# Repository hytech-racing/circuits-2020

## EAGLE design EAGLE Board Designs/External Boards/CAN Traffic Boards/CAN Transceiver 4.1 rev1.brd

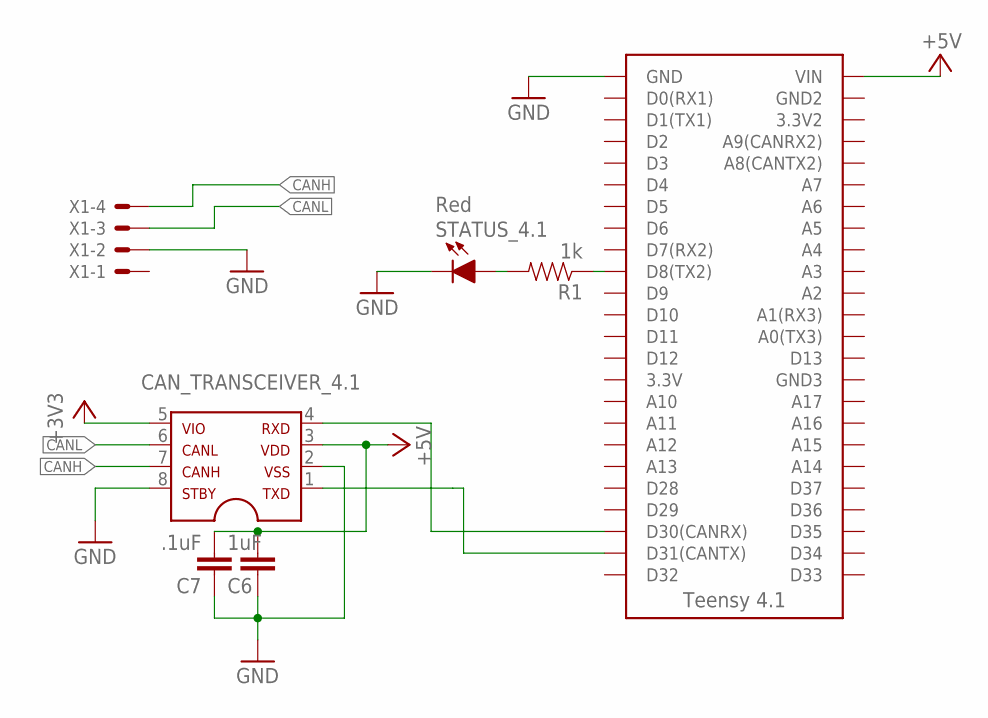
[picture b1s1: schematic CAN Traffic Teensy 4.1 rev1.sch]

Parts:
C6: 1uF; 0603-CAP
C7: .1uF; 0603-CAP
CAN_TRANSCEIVER_4.1: MCP2562SOIC-08; SOIC-08
R1: 1k; 0603-RES
STATUS_4.1: Red; LED-805
U$2: TEENSY_4.1_SIMPLE
X1: CONNECTOR-4NANO-FIT_RIGHT_ANGLE-4-SURFACE; NANO-FIT_RIGHT_ANGLE-4-SURFACE

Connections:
+3V3: CAN_TRANSCEIVER_4.1.5
+5V: C6.1, C7.1, CAN_TRANSCEIVER_4.1.3, U$2.VIN
CANH: CAN_TRANSCEIVER_4.1.7, X1.4
CANL: CAN_TRANSCEIVER_4.1.6, X1.3
GND: C6.2, C7.2, CAN_TRANSCEIVER_4.1.2, STATUS_4.1.C, U$2.GND, X1.2
unnamed: CAN_TRANSCEIVER_4.1.4, U$2.D30(CANRX)
unnamed: CAN_TRANSCEIVER_4.1.1, U$2.D31(CANTX)
unnamed: R1.2, STATUS_4.1.A
unnamed: R1.1, U$2.D8(TX2)

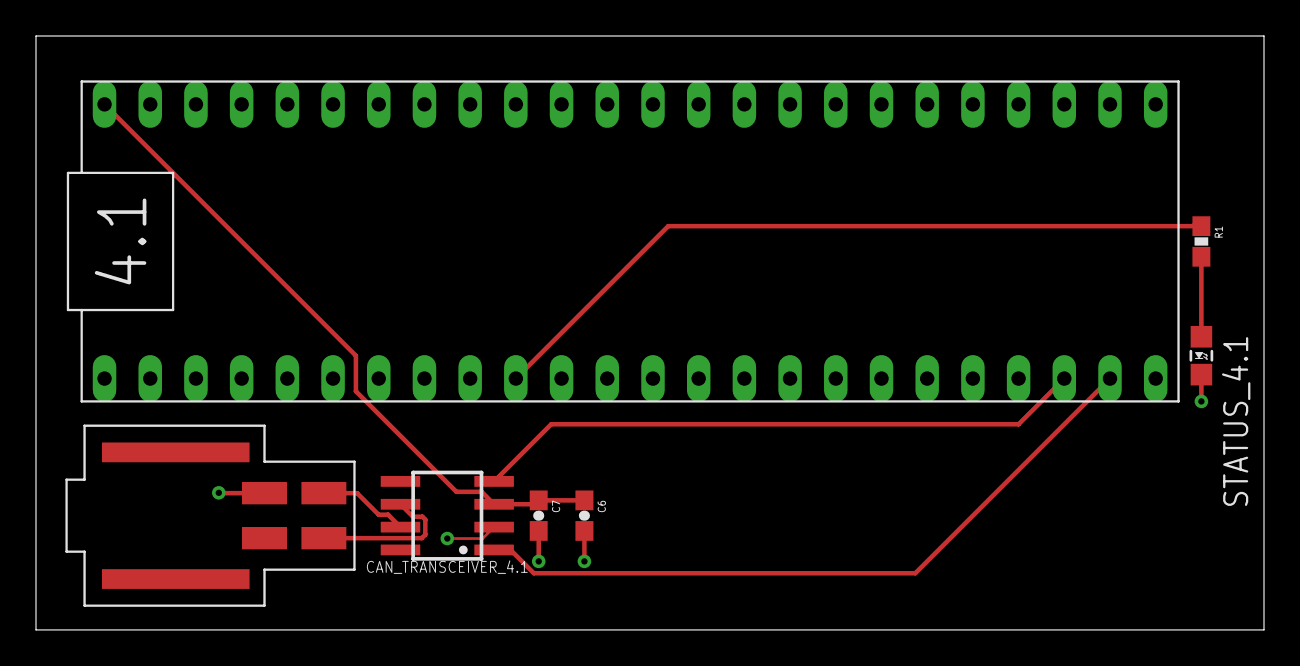
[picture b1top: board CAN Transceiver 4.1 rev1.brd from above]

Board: 2 copper layers, 68.2 x 33.0 mm, 7 parts (0 on the bottom side), 8 nets.

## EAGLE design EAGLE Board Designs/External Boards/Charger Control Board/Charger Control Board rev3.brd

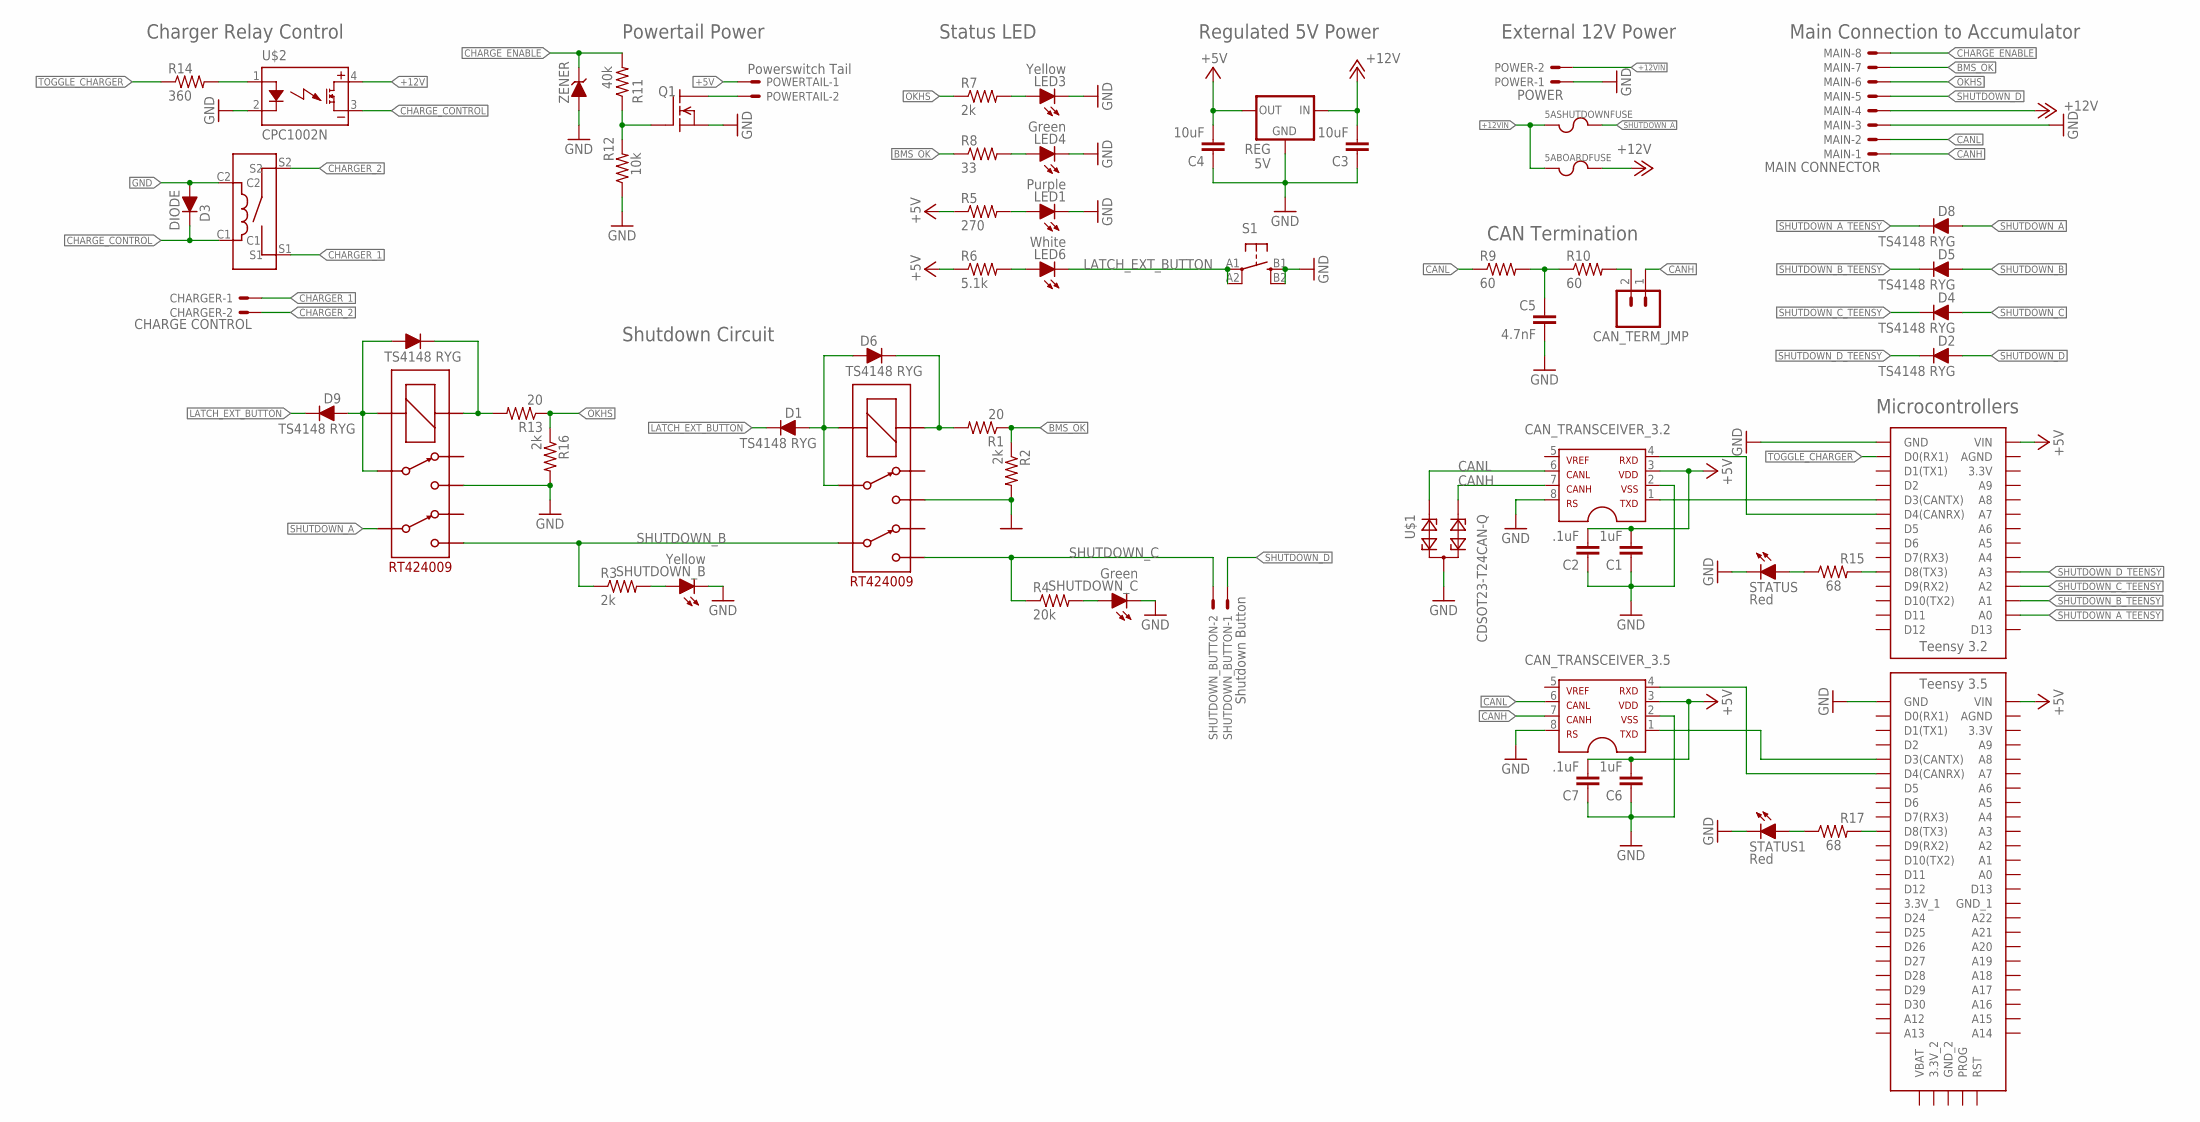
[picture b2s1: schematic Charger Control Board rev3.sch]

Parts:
5ABOARDFUSE, 5ASHUTDOWNFUSE: FUSE_MINIBLADE; MINI-BLADE_FUSE_HOLDER; RATING 5A
BMS_SHUTDOWN_RLY: RT424009; RELAY_DPDT
C1, C6: 1uF; 0805; TOLERANCE 5%; VOLTAGE 10V
C2, C7: .1uF; 0805; TOLERANCE 5%; VOLTAGE 10V
C3: 10uF; 0805; TOLERANCE 1%; VOLTAGE 25V
C4: 10uF; 0805; TOLERANCE 5%; VOLTAGE 25V
C5: 4.7nF; 0805; TOLERANCE 5%; VOLTAGE 50V
CAN_TERM_JMP: M02_SLIM; 1X02_SLIM
CAN_TRANSCEIVER_3.2, CAN_TRANSCEIVER_3.5: MCP2551; SOIC-08
CHARGER: CHARGE CONTROL; NANO-FIT_VERTICAL-2
D1, D2, D4, D5, D6, D7, D8, D9: TS4148 RYG; 0805_D
D3: DIODE; 0805_D
IMD_SHUTDOWN_RLY: RT424009; RELAY_DPDT
LED1: Purple; LED-805
LED3: Yellow; LED-805
LED4: Green; LED-805
LED6: White; LED-805
MAIN: MAIN CONNECTOR; NANO-FIT_VERTICAL-8
POWER: POWER; NANO-FIT_VERTICAL-2
POWERTAIL: Powerswitch Tail; NANO-FIT_VERTICAL-2
Q1: DMG3406LSOT; SOT23
R1, R13: 20; 0805; TOLERANCE 1%
R2, R3, R7, R16: 2k; 0805; TOLERANCE 1%
R4: 20k; 0805; TOLERANCE 1%
R5: 270; 0805; TOLERANCE 1%
R6: 5.1k; 0805; TOLERANCE 1%
R8: 33; 0805; TOLERANCE 1%
R9, R10: 60; 0805; TOLERANCE 1%
R11: 40k; 0805; TOLERANCE 1%
R12: 10k; 0805; TOLERANCE 1%
R14: 360; 0805; TOLERANCE 1%
R15, R17: 68; 0805; TOLERANCE 1%
REG: 5V; OKI-78SR
S1: BTN_10-XXSMD; TACTILE_SWITCH_SMD_6.2MM_TALL
SHUTDOWN_B: Yellow; LED-805
SHUTDOWN_BUTTON: Shutdown Button; NANO-FIT_VERTICAL-2
SHUTDOWN_C: Green; LED-805
STATUS, STATUS1: Red; LED-805
U$1: CDSOT23-T24CAN-Q; SOT23
U$2: CPC1002N; SOP04
U$3: KT12-1A-40L-THT
U$4: TEENSY_3.2_SIMPLE
U$5: TEENSY_3.5_EXT
ZENER: DIODE_ZENER; SOT23

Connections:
+5V: C1.2, C2.2, C4.2, C6.2, C7.2, CAN_TRANSCEIVER_3.2.3, CAN_TRANSCEIVER_3.5.3, POWERTAIL.P$1, R5.1, R6.1, REG.3 (OUT), U$4.VIN, U$5.VIN
+12V: 5ABOARDFUSE.R1 (2), 5ABOARDFUSE.R2 (2), C3.2, MAIN.P$4, REG.1 (IN), U$2.4 (DC+)
+12VIN: 5ABOARDFUSE.L1 (1), 5ABOARDFUSE.L2 (1), 5ASHUTDOWNFUSE.L1 (1), 5ASHUTDOWNFUSE.L2 (1), POWER.P$2
BMS_OK: MAIN.P$7, R1.1, R2.1, R8.1
BMS_OK_RELAY: BMS_SHUTDOWN_RLY.COIL+, D6.C, R1.2
BMS_PWR_STEP: BMS_SHUTDOWN_RLY.3, BMS_SHUTDOWN_RLY.COIL-, D1.A, D6.A
CANH: CAN_TERM_JMP.1, CAN_TRANSCEIVER_3.2.7, CAN_TRANSCEIVER_3.5.7, MAIN.P$1, U$1.2
CANL: CAN_TRANSCEIVER_3.2.6, CAN_TRANSCEIVER_3.5.6, MAIN.P$2, R9.1, U$1.1
CHARGER_1: CHARGER.P$1, U$3.S1
CHARGER_2: CHARGER.P$2, U$3.S2
CHARGE_CONTROL: D3.C, U$2.3 (DC-), U$3.C1
CHARGE_ENABLE: MAIN.P$8, R11.2, ZENER.3 (C)
GND: C1.1, C2.1, C3.1, C4.1, C5.2, C6.1, C7.1, CAN_TRANSCEIVER_3.2.2, CAN_TRANSCEIVER_3.2.8, CAN_TRANSCEIVER_3.5.2, CAN_TRANSCEIVER_3.5.8, D3.A, LED1.C, LED3.C, LED4.C, MAIN.P$3, POWER.P$1, Q1.2 (S), R12.1, REG.2 (GND), S1.B1 (S), S1.B2 (S1), SHUTDOWN_B.C, SHUTDOWN_C.C, STATUS.C, STATUS1.C, U$1.3, U$2.2 (CONTROL-), U$3.C2, U$4.GND, U$5.GND, ZENER.1 (A)
IMD_PWR_STEP: D7.A, D9.A, IMD_SHUTDOWN_RLY.3, IMD_SHUTDOWN_RLY.COIL-
LATCH_EXT_BUTTON: D1.C, D9.C, LED6.C, S1.A1, S1.A2 (P1)
unnamed: POWERTAIL.P$2, Q1.3 (D)
unnamed: LED6.A, R6.2
unnamed: LED4.A, R8.2
unnamed: CAN_TRANSCEIVER_3.5.4, U$5.D4(CANRX)
unnamed: Q1.1 (G), R11.1, R12.2
unnamed: CAN_TRANSCEIVER_3.5.1, U$5.D3(CANTX)
unnamed: R17.1, STATUS1.A
unnamed: R15.1, STATUS.A
unnamed: R17.2, U$5.D8(TX3)
unnamed: R14.2, U$2.1 (CONTROL+)
unnamed: R15.2, U$4.D8(TX3)
unnamed: D7.C, IMD_SHUTDOWN_RLY.COIL+, R13.2
unnamed: CAN_TRANSCEIVER_3.2.4, U$4.D4(CANRX)
unnamed: CAN_TERM_JMP.2, R10.2
unnamed: R3.2, SHUTDOWN_B.A
unnamed: CAN_TRANSCEIVER_3.2.1, U$4.D3(CANTX)
unnamed: LED3.A, R7.2
unnamed: LED1.A, R5.2
unnamed: R4.2, SHUTDOWN_C.A
unnamed: BMS_SHUTDOWN_RLY.4, IMD_SHUTDOWN_RLY.4, R2.2, R16.2
unnamed: C5.1, R9.2, R10.1
OKHS: MAIN.P$6, R7.1, R13.1, R16.1
SHUTDOWN_A: 5ASHUTDOWNFUSE.R1 (2), 5ASHUTDOWNFUSE.R2 (2), D8.A, IMD_SHUTDOWN_RLY.6
SHUTDOWN_A_TEENSY: D8.C, U$4.A0
SHUTDOWN_B: BMS_SHUTDOWN_RLY.6, D5.A, IMD_SHUTDOWN_RLY.5, R3.1
SHUTDOWN_B_TEENSY: D5.C, U$4.A1
SHUTDOWN_C: BMS_SHUTDOWN_RLY.5, D4.A, R4.1, SHUTDOWN_BUTTON.P$2
SHUTDOWN_C_TEENSY: D4.C, U$4.A2
SHUTDOWN_D: D2.A, MAIN.P$5, SHUTDOWN_BUTTON.P$1
SHUTDOWN_D_TEENSY: D2.C, U$4.A3
TOGGLE_CHARGER: R14.1, U$4.D0(RX1)

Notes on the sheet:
Main Connection to Accumulator
External 12V Power
Powertail Power
Charger Relay Control
Regulated 5V Power
CAN Termination
Microcontrollers
Shutdown Circuit
Status LED

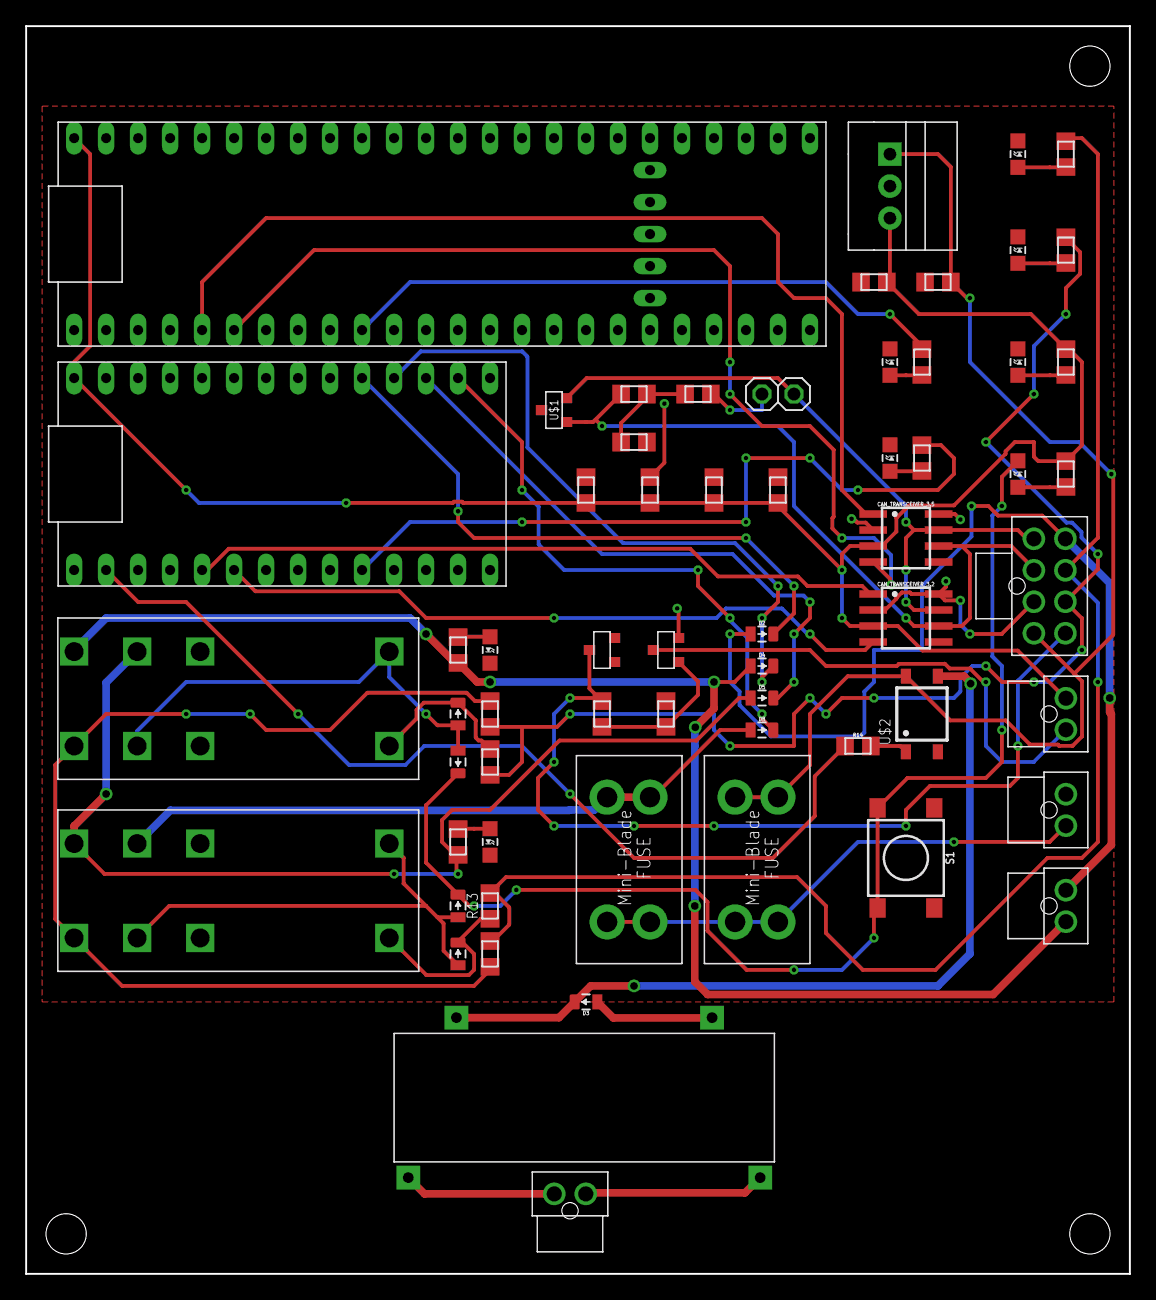
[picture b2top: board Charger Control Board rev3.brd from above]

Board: 2 copper layers, 87.6 x 99.1 mm, 62 parts (0 on the bottom side), 46 nets.

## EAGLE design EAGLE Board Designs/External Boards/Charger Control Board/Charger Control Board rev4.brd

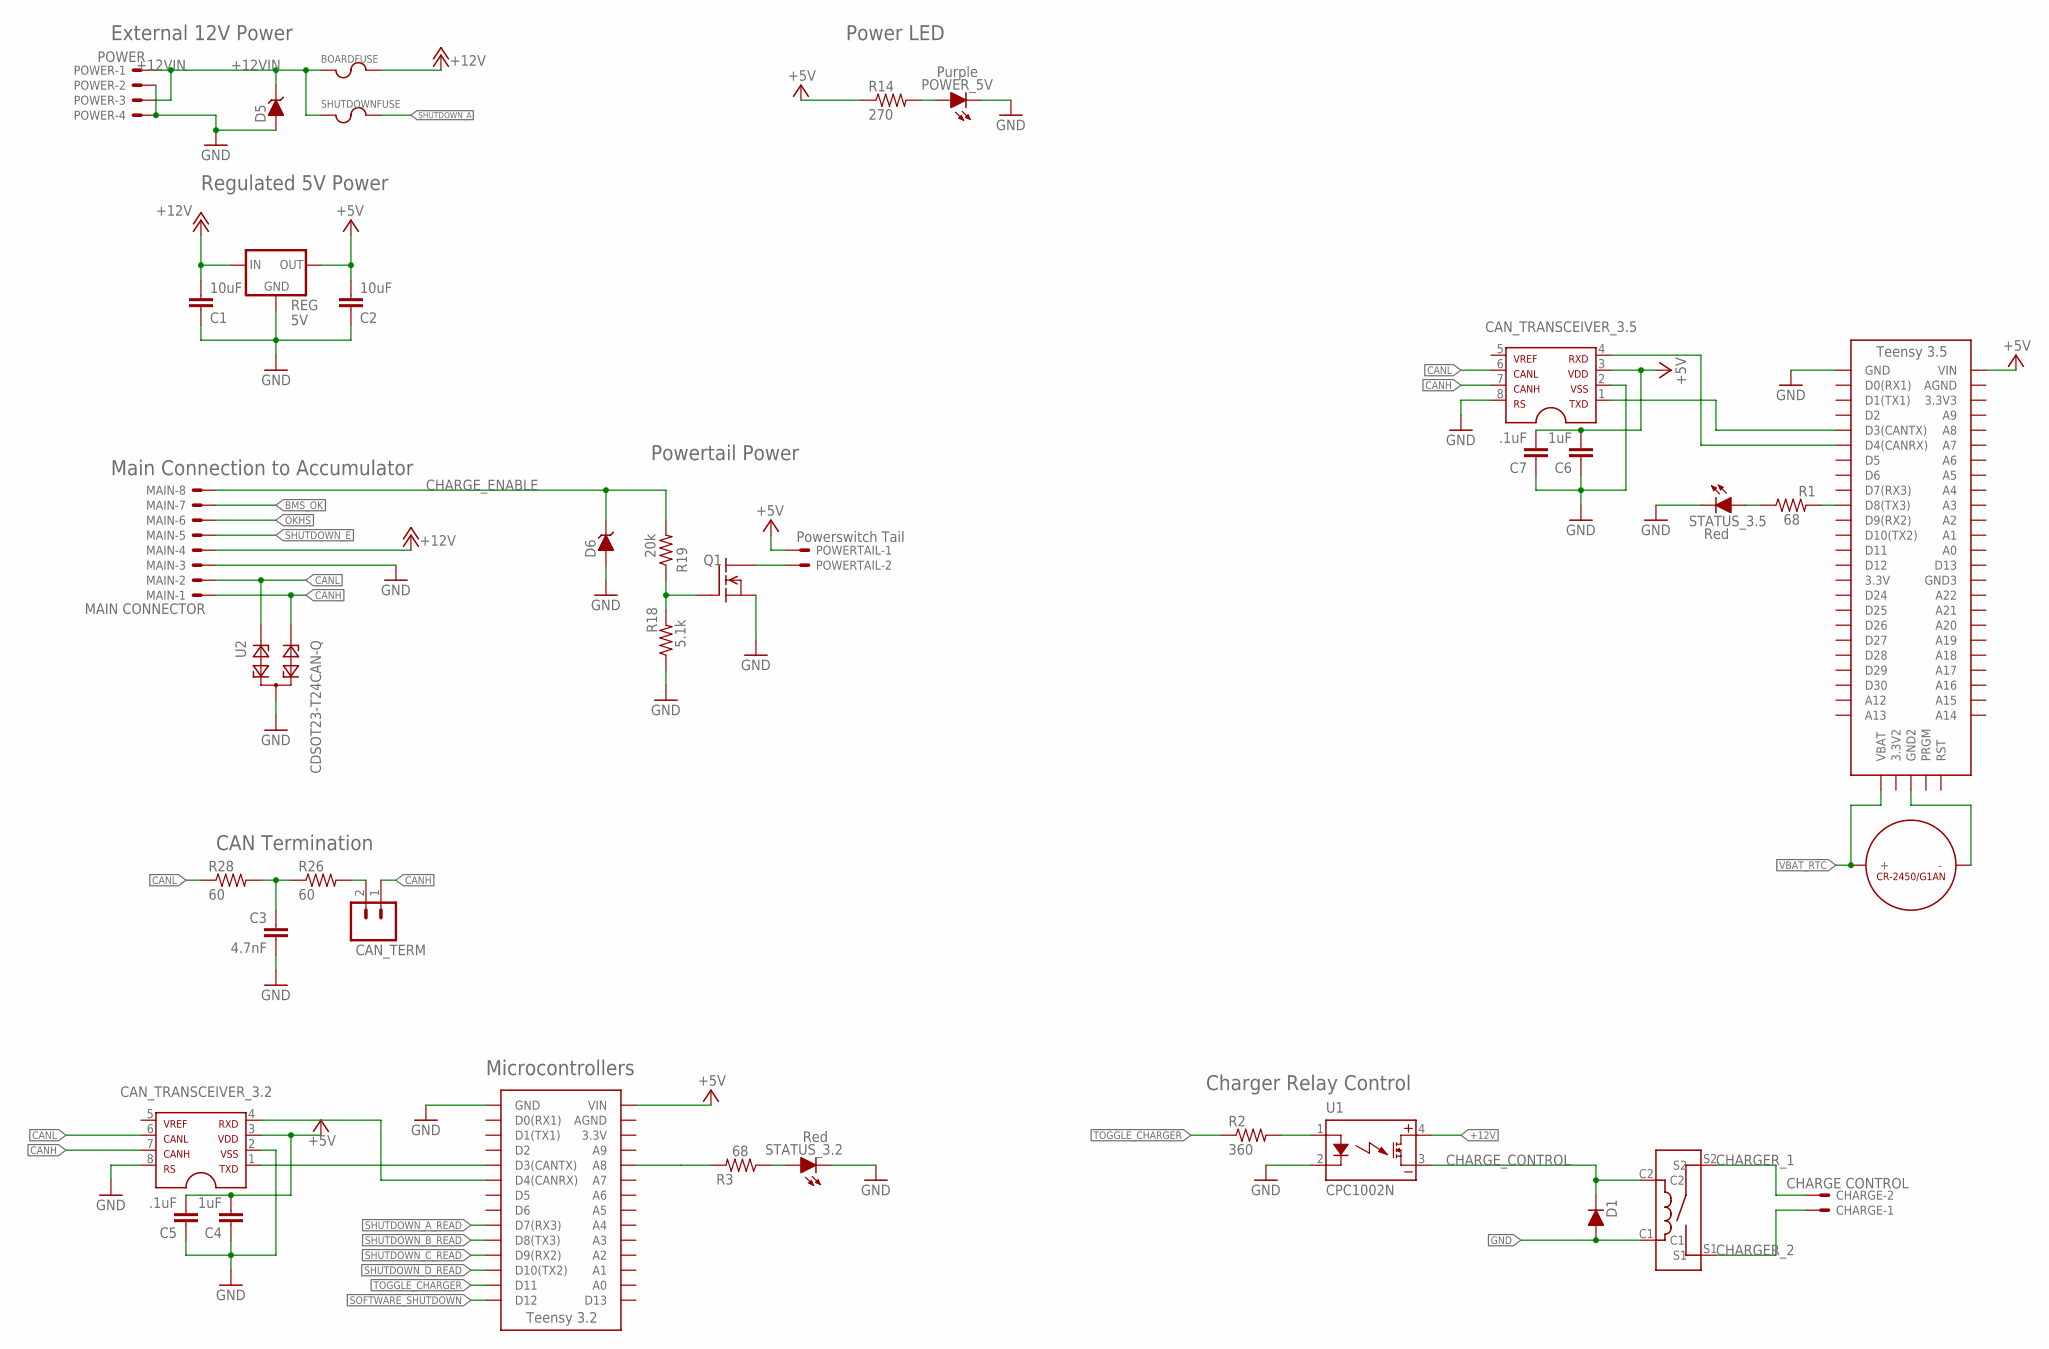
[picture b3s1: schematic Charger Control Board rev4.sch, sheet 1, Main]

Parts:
$$U$3: CR-2450/G1AN
BOARDFUSE: FUSE_MINIBLADE; MINI-BLADE_FUSE_HOLDER; RATING 3A
C1: 10uF; 0603-CAP; TOLERANCE 1%; VOLTAGE 25V
C2: 10uF; 0603-CAP; TOLERANCE 5%; VOLTAGE 25V
C3: 4.7nF; 0603-CAP; TOLERANCE 5%; VOLTAGE 50V
C4, C6: 1uF; 0603-CAP; TOLERANCE 5%; VOLTAGE 10V
C5, C7: .1uF; 0603-CAP; TOLERANCE 5%; VOLTAGE 10V
CAN_TERM: M02_SLIM; 1X02_SLIM
CAN_TRANSCEIVER_3.2, CAN_TRANSCEIVER_3.5: MCP2551; SOIC-08
CHARGE: CHARGE CONTROL; NANO-FIT_VERTICAL-2
D1: DIODE; 0805_D
D5: DIODE_ZENER0603; 0603_D
D6: DIODE_ZENER; SOT23
MAIN: MAIN CONNECTOR; NANO-FIT_VERTICAL-8
POWER: POWER; NANO-FIT_VERTICAL-4
POWERTAIL: Powerswitch Tail; NANO-FIT_VERTICAL-2
POWER_5V: Purple; LED-805
Q1: DMG3406LSOT; SOT23
R1, R3: 68; 0603-RES; TOLERANCE 1%
R2: 360; 0603-RES; TOLERANCE 1%
R14: 270; 0603-RES; TOLERANCE 1%
R18: 5.1k; 0603-RES; TOLERANCE 1%
R19: 20k; 0603-RES; TOLERANCE 1%
R26, R28: 60; 0603-RES; TOLERANCE 1%
REG: 5V; OKI-78SR
SHUTDOWNFUSE: FUSE_MINIBLADE; MINI-BLADE_FUSE_HOLDER; RATING 4A
STATUS_3.2, STATUS_3.5: Red; LED-805
U1: CPC1002N; SOP04
U2: CDSOT23-T24CAN-Q; SOT23
U$3: TEENSY_3.5_EXT_RTC
U$4: TEENSY_3.2_SIMPLE
U$5: KT12-1A-40L-THT

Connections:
+5V: C2.2, C4.2, C5.2, C6.2, C7.2, CAN_TRANSCEIVER_3.2.3, CAN_TRANSCEIVER_3.5.3, POWERTAIL.P$1, R14.1, REG.3 (OUT), U$3.VIN, U$4.VIN; also elsewhere on the board
+12V: BOARDFUSE.R1 (2), BOARDFUSE.R2 (2), C1.2, MAIN.P$4, REG.1 (IN), U1.4 (DC+); also elsewhere on the board
+12VIN: BOARDFUSE.L1 (1), BOARDFUSE.L2 (1), D5.C, POWER.P$1, POWER.P$3, SHUTDOWNFUSE.L1 (1), SHUTDOWNFUSE.L2 (1)
BMS_OK: MAIN.P$7; also elsewhere on the board
CANH: CAN_TERM.1, CAN_TRANSCEIVER_3.2.7, CAN_TRANSCEIVER_3.5.7, MAIN.P$1, U2.2
CANL: CAN_TRANSCEIVER_3.2.6, CAN_TRANSCEIVER_3.5.6, MAIN.P$2, R28.1, U2.1
CHARGER_1: CHARGE.P$1, U$5.S1
CHARGER_2: CHARGE.P$2, U$5.S2
CHARGE_CONTROL: D1.C, U1.3 (DC-), U$5.C2
CHARGE_ENABLE: D6.3 (C), MAIN.P$8, R19.2
GND: C1.1, C2.1, C3.2, C4.1, C5.1, C6.1, C7.1, CAN_TRANSCEIVER_3.2.2, CAN_TRANSCEIVER_3.2.8, CAN_TRANSCEIVER_3.5.2, CAN_TRANSCEIVER_3.5.8, D1.A, D5.A, D6.1 (A), MAIN.P$3, POWER.P$2, POWER.P$4, POWER_5V.C, Q1.2 (S), R18.1, REG.2 (GND), STATUS_3.2.C, STATUS_3.5.C, U1.2 (CONTROL-), U2.3, U$3.GND, U$4.GND, U$5.C1; also elsewhere on the board
unnamed: POWERTAIL.P$2, Q1.3 (D)
unnamed: CAN_TRANSCEIVER_3.5.4, U$3.D4(CANRX)
unnamed: Q1.1 (G), R18.2, R19.1
unnamed: CAN_TRANSCEIVER_3.5.1, U$3.D3(CANTX)
unnamed: R1.1, STATUS_3.5.A
unnamed: R3.1, STATUS_3.2.A
unnamed: R1.2, U$3.D8(TX3)
unnamed: R2.2, U1.1 (CONTROL+)
unnamed: R3.2, U$4.A8
unnamed: CAN_TRANSCEIVER_3.2.4, U$4.D4(CANRX)
unnamed: CAN_TERM.2, R26.2
unnamed: CAN_TRANSCEIVER_3.2.1, U$4.D3(CANTX)
unnamed: POWER_5V.A, R14.2
unnamed: $$U$3.-, U$3.GND2
unnamed: C3.1, R26.1, R28.2
OKHS: MAIN.P$6; also elsewhere on the board
SHUTDOWN_A: SHUTDOWNFUSE.R1 (2), SHUTDOWNFUSE.R2 (2); also elsewhere on the board
SHUTDOWN_A_READ: U$4.D7(RX3); also elsewhere on the board
SHUTDOWN_B_READ: U$4.D8(TX3); also elsewhere on the board
SHUTDOWN_C_READ: U$4.D9(RX2); also elsewhere on the board
SHUTDOWN_D_READ: U$4.D10(TX2); also elsewhere on the board
SHUTDOWN_E: MAIN.P$5; also elsewhere on the board
SOFTWARE_SHUTDOWN: U$4.D12; also elsewhere on the board
TOGGLE_CHARGER: R2.1, U$4.D11
VBAT_RTC: $$U$3.+_0 (+), $$U$3.+_1 (+), U$3.VBAT

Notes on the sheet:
Main Connection to Accumulator
Powertail Power
Charger Relay Control
CAN Termination
Microcontrollers
Power LED
External 12V Power
Regulated 5V Power

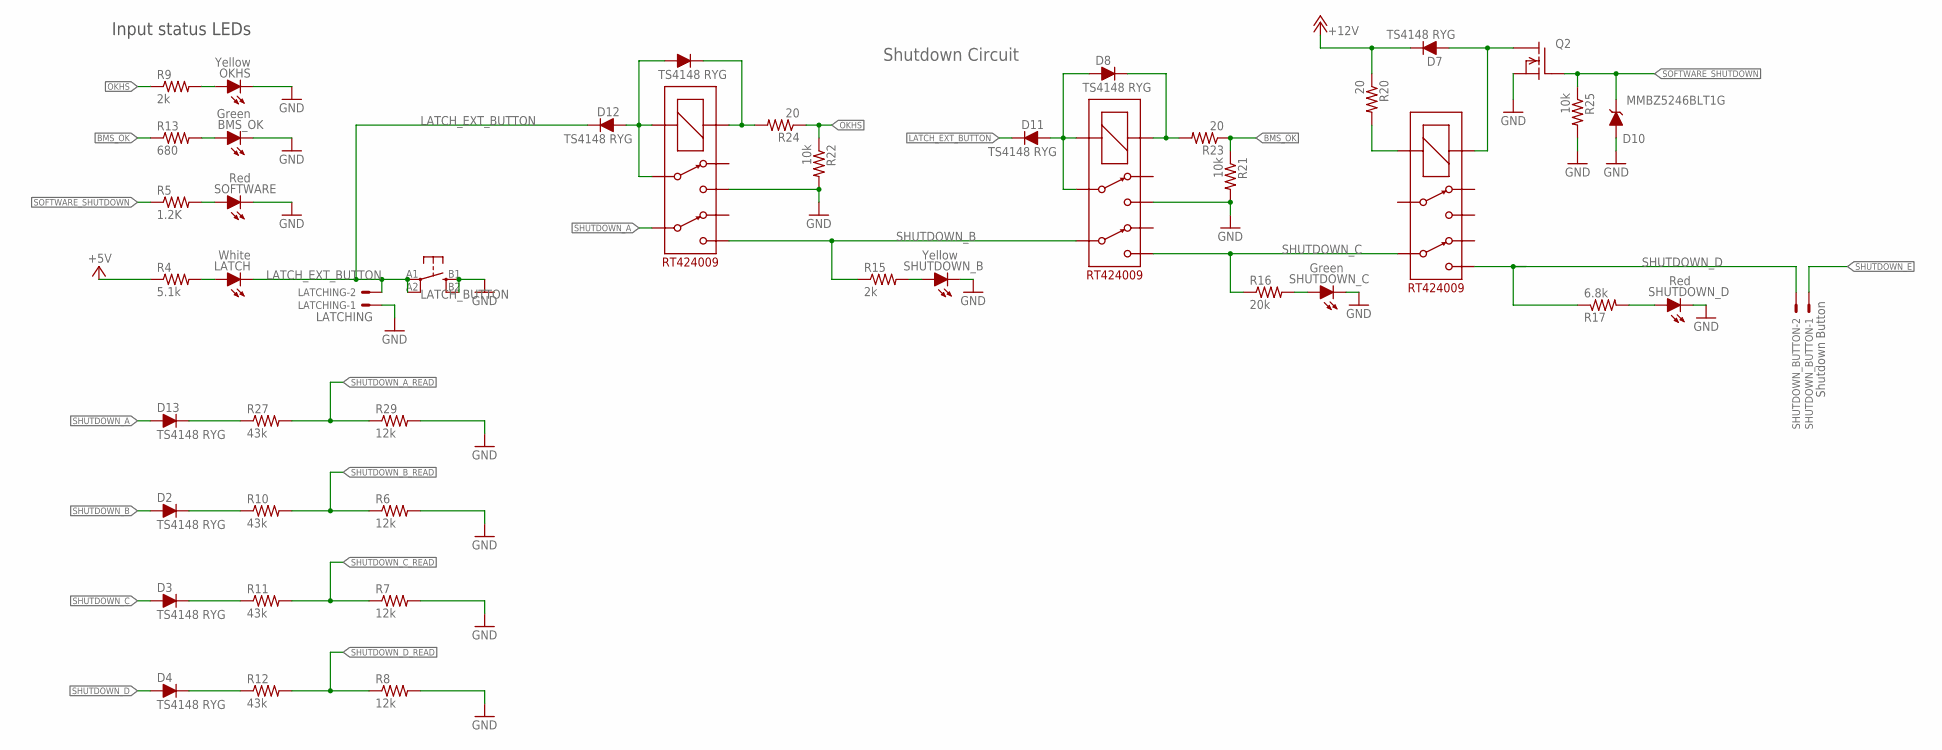
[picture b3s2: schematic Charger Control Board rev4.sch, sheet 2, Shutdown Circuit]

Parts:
BMS_OK: Green; LED-805
BMS_SHUTDOWN_RLY, BMS_SHUTDOWN_RLY1: RT424009; RELAY_DPDT
D2, D3, D4, D7, D8, D9, D11, D12, D13: TS4148 RYG; 0805_D
D10: MMBZ5246BLT1G; SOT23
IMD_SHUTDOWN_RLY: RT424009; RELAY_DPDT
LATCH: White; LED-805
LATCHING: LATCHING; NANO-FIT_VERTICAL-2
LATCH_BUTTON: BTN_10-XXSMD; TACTILE_SWITCH_SMD_6.2MM_TALL
OKHS: Yellow; LED-805
Q2: DMG3406LSOT; SOT23
R4: 5.1k; 0603-RES; TOLERANCE 1%
R5: 1.2K; 0603-RES
R6, R7, R8, R29: 12k; 0603-RES
R9, R15: 2k; 0603-RES; TOLERANCE 1%
R10, R11, R12, R27: 43k; 0603-RES
R13: 680; 0603-RES; TOLERANCE 1%
R16: 20k; 0603-RES; TOLERANCE 1%
R17: 6.8k; 0603-RES
R20, R23, R24: 20; 0603-RES; TOLERANCE 1%
R21, R22: 10k; 0603-RES; TOLERANCE 1%
R25: 10k; 0603-RES
SHUTDOWN_B: Yellow; LED-805
SHUTDOWN_BUTTON: Shutdown Button; NANO-FIT_VERTICAL-2
SHUTDOWN_C: Green; LED-805
SHUTDOWN_D: Red; LED-805
SOFTWARE: Red; LED-805

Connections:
+5V: R4.1; also elsewhere on the board
+12V: D7.C, R20.1; also elsewhere on the board
BMS_OK: R13.1, R21.1, R23.1; also elsewhere on the board
BMS_OK_RELAY: BMS_SHUTDOWN_RLY.COIL+, D8.C, R23.2
BMS_PWR_STEP: BMS_SHUTDOWN_RLY.3, BMS_SHUTDOWN_RLY.COIL-, D8.A, D11.A
GND: BMS_OK.C, BMS_SHUTDOWN_RLY.4, D10.1 (A), IMD_SHUTDOWN_RLY.4, LATCHING.P$1, LATCH_BUTTON.B1 (S), LATCH_BUTTON.B2 (S1), OKHS.C, Q2.2 (S), R6.2, R7.2, R8.2, R21.2, R22.2, R25.2, R29.2, SHUTDOWN_B.C, SHUTDOWN_C.C, SHUTDOWN_D.C, SOFTWARE.C; also elsewhere on the board
IMD_PWR_STEP: D9.A, D12.A, IMD_SHUTDOWN_RLY.3, IMD_SHUTDOWN_RLY.COIL-
LATCH_EXT_BUTTON: D11.C, D12.C, LATCH.C, LATCHING.P$2, LATCH_BUTTON.A1, LATCH_BUTTON.A2 (P1)
unnamed: LATCH.A, R4.2
unnamed: BMS_OK.A, R13.2
unnamed: D9.C, IMD_SHUTDOWN_RLY.COIL+, R24.2
unnamed: BMS_SHUTDOWN_RLY1.COIL-, R20.2
unnamed: D13.C, R27.1
unnamed: D2.C, R10.1
unnamed: R15.2, SHUTDOWN_B.A
unnamed: D3.C, R11.1
unnamed: D4.C, R12.1
unnamed: OKHS.A, R9.2
unnamed: R17.2, SHUTDOWN_D.A
unnamed: R5.2, SOFTWARE.A
unnamed: R16.2, SHUTDOWN_C.A
unnamed: BMS_SHUTDOWN_RLY1.COIL+, D7.A, Q2.3 (D)
OKHS: R9.1, R22.1, R24.1; also elsewhere on the board
SHUTDOWN_A: D13.A, IMD_SHUTDOWN_RLY.6; also elsewhere on the board
SHUTDOWN_A_READ: R27.2, R29.1; also elsewhere on the board
SHUTDOWN_B: BMS_SHUTDOWN_RLY.6, D2.A, IMD_SHUTDOWN_RLY.5, R15.1
SHUTDOWN_B_READ: R6.1, R10.2; also elsewhere on the board
SHUTDOWN_C: BMS_SHUTDOWN_RLY.5, BMS_SHUTDOWN_RLY1.6, D3.A, R16.1
SHUTDOWN_C_READ: R7.1, R11.2; also elsewhere on the board
SHUTDOWN_D: BMS_SHUTDOWN_RLY1.5, D4.A, R17.1, SHUTDOWN_BUTTON.P$2
SHUTDOWN_D_READ: R8.1, R12.2; also elsewhere on the board
SHUTDOWN_E: SHUTDOWN_BUTTON.P$1; also elsewhere on the board
SOFTWARE_SHUTDOWN: D10.3 (C), Q2.1 (G), R5.1, R25.1; also elsewhere on the board

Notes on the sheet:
Shutdown Circuit
Input status LEDs

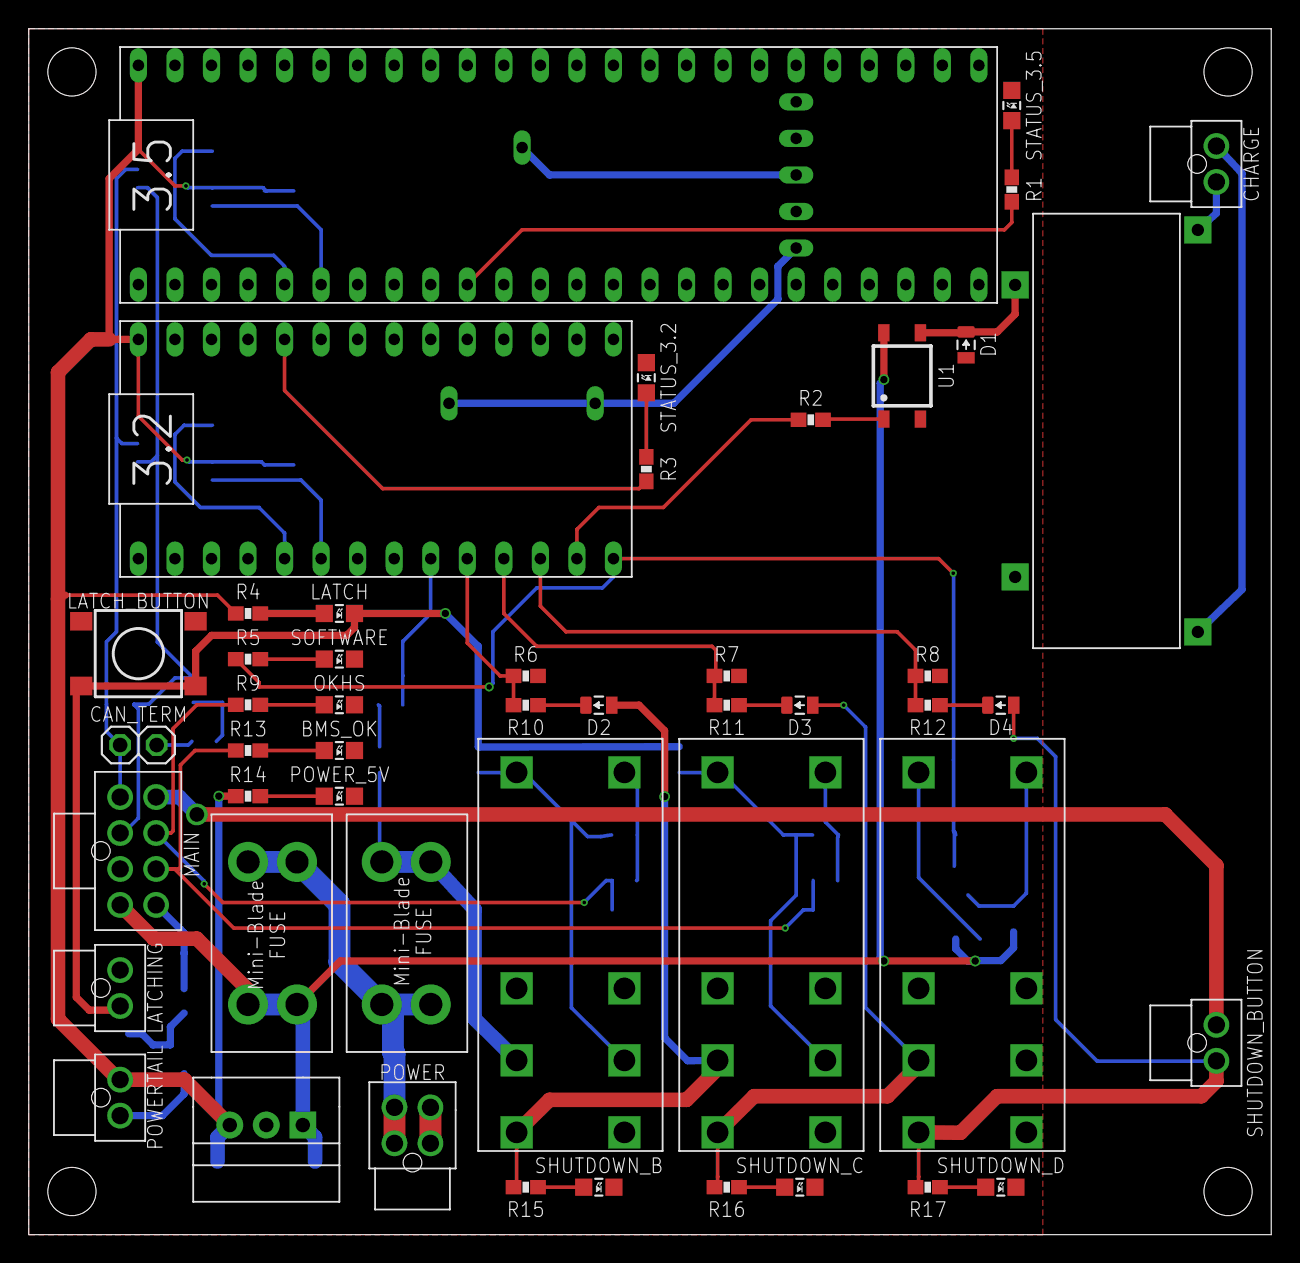
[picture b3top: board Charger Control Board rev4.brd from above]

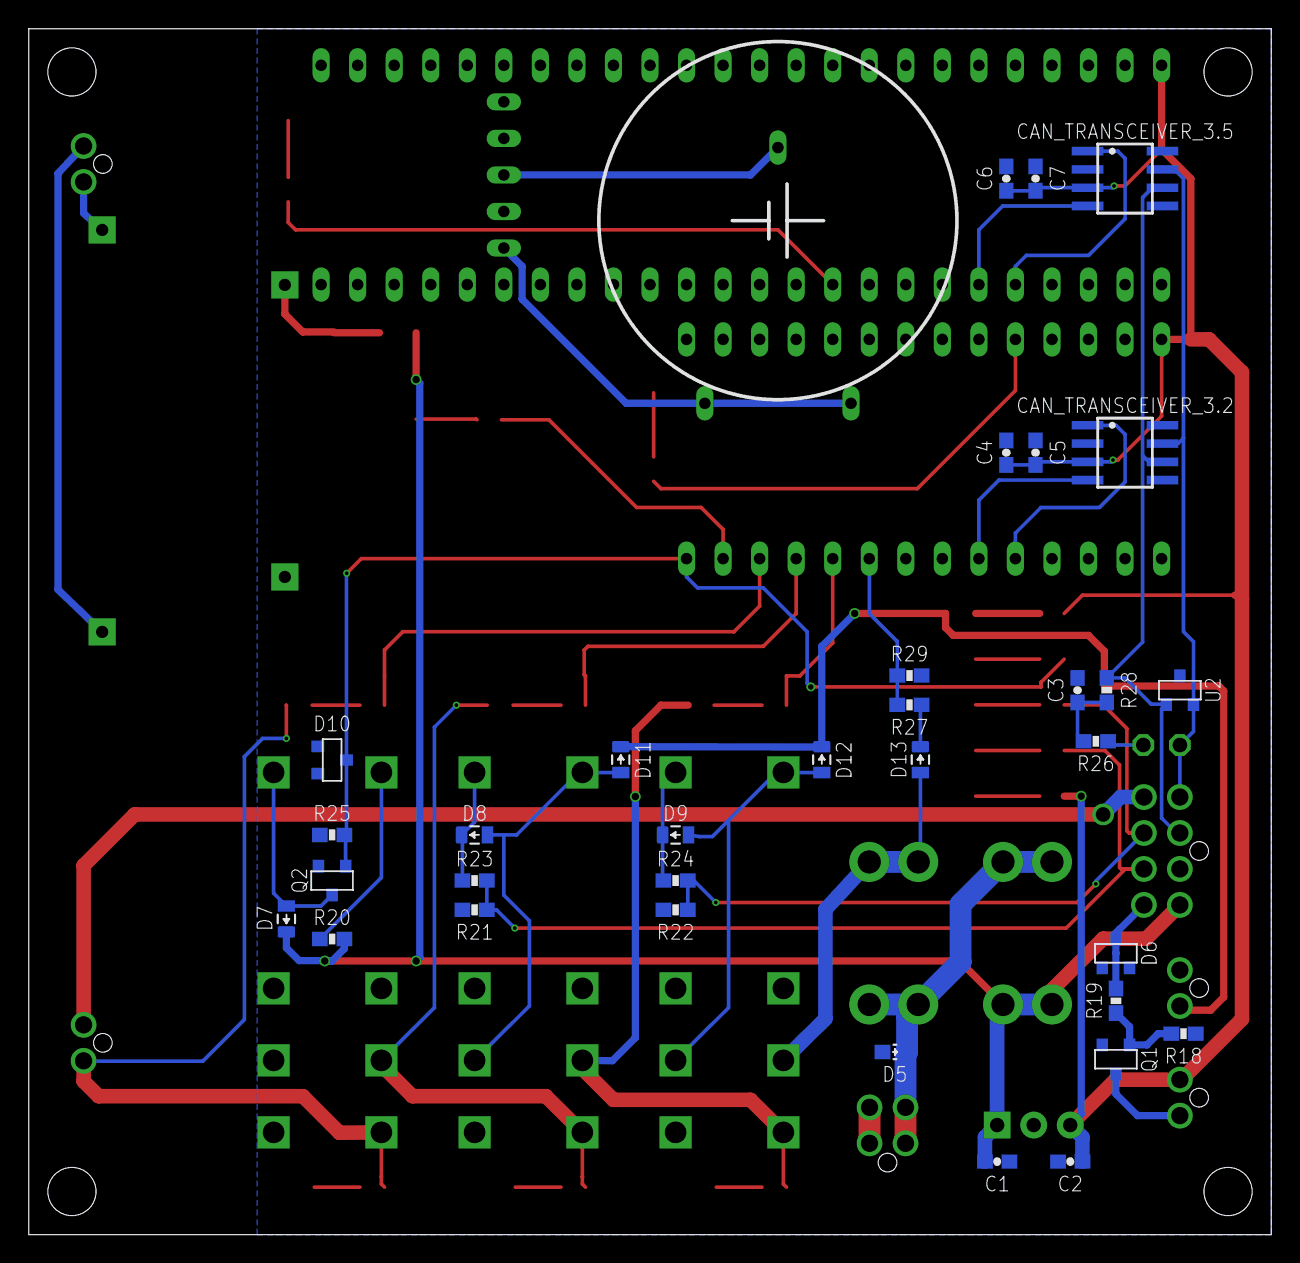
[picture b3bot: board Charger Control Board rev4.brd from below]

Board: 2 copper layers, 86.4 x 83.8 mm, 87 parts (34 on the bottom side), 57 nets.

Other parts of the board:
$$U$1, $$U$2: M3_MOUNTING
U$1, U$2: M3_MOUNTING
